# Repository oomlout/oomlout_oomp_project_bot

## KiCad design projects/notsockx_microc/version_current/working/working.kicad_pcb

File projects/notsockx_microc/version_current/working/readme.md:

# microc by notsockx  
This is a harvested standardized copy of a project from github.  
The original project can be found at:  
https://github.com/notsockx/microc  
Please consult that link for additional, details, files, and license information.  
Note: It was auto harvested and if the original repo had more than one board file or anything out of the ordinary the files here are likely not representative.

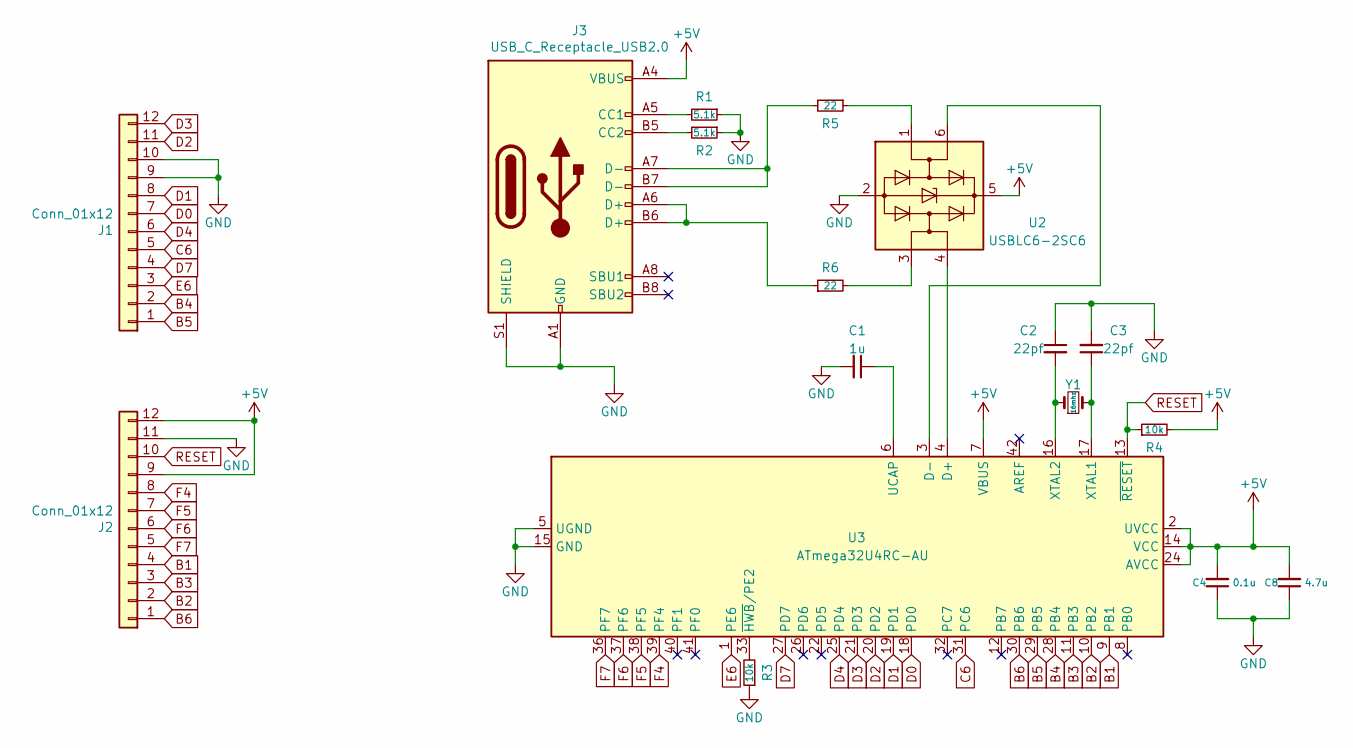
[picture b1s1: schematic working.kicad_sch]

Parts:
C1: 1u; C_0603_1608Metric
C2, C3: 22pf; C_0603_1608Metric
C4: 0.1u; C_0603_1608Metric
C8: 4.7u; C_0603_1608Metric
J1, J2: Conn_01x12; PinSocket_1x12_P2.54mm_Vertical
J3: USB_C_Receptacle_USB2.0; USB-C_16P_Midmount
R1, R2: 5.1k; R_0603_1608Metric
R3, R4: 10k; R_0603_1608Metric
R5, R6: 22; R_0603_1608Metric
U2: USBLC6-2SC6; SOT-23-6
U3: ATmega32U4RC-AU; TQFP-44_10x10mm_P0.8mm
Y1: 16mhz; Crystal_SMD_5032-2Pin_5.0x3.2mm_HandSoldering

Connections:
B1: J2.4, U3.9 (PB1)
B2: J2.2, U3.10 (PB2)
B3: J2.3, U3.11 (PB3)
B4: J1.2, U3.28 (PB4)
B5: J1.1, U3.29 (PB5)
B6: J2.1, U3.30 (PB6)
C6: J1.5, U3.31 (PC6)
D0: J1.7, U3.18 (PD0)
D1: J1.8, U3.19 (PD1)
D2: J1.11, U3.20 (PD2)
D3: J1.12, U3.21 (PD3)
D4: J1.6, U3.25 (PD4)
D7: J1.4, U3.27 (PD7)
E6: J1.3, U3.1 (PE6)
F4: J2.8, U3.39 (PF4)
F5: J2.7, U3.38 (PF5)
F6: J2.6, U3.37 (PF6)
F7: J2.5, U3.36 (PF7)
GND: C1.2, C2.1, C3.2, C4.1, C8.1, J1.9, J1.10, J2.11, J3.A1 (GND), J3.A12 (GND), J3.B1 (GND), J3.B12 (GND), J3.S1 (SHIELD), R3.1, U2.2 (GND), U3.5 (UGND), U3.15 (GND), U3.23 (GND), U3.35 (GND), U3.43 (GND)
unnamed: C1.1, U3.6 (UCAP)
unnamed: C2.2, U3.16 (XTAL2), Y1.1
unnamed: C3.1, U3.17 (XTAL1), Y1.2
unnamed: J3.A5 (CC1), R1.2
unnamed: J3.A6 (D+), J3.B6 (D+), R6.1
unnamed: J3.A7 (D-), J3.B7 (D-), R5.2
unnamed: J3.B5 (CC2), R2.2
unnamed: R3.2, U3.33 (~HWB/PE2)
unnamed: R5.1, U2.1 (I/O1)
unnamed: R6.2, U2.3 (I/O2)
unnamed: U2.4 (I/O2), U3.4 (D+)
unnamed: U2.6 (I/O1), U3.3 (D-)
RESET: J2.10, R4.1, U3.13 (~RESET)

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
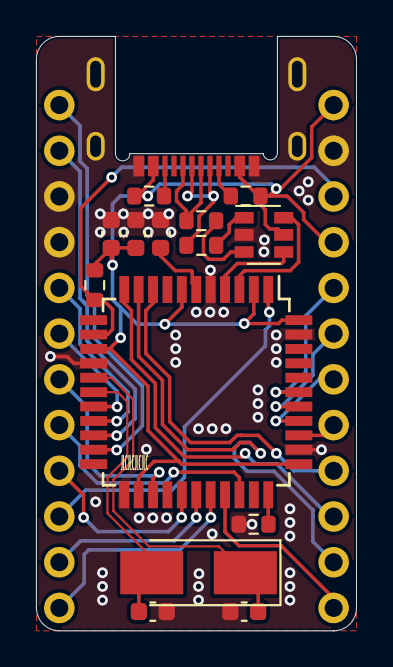
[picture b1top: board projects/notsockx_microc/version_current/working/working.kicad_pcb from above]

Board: 2 copper layers, 17.8 x 33.0 mm, 17 parts (0 on the bottom side), 33 nets.

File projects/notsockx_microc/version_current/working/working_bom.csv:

"Id";"Designator";"Footprint";"Quantity";"Designation";"Supplier and ref";
1;"J2,J1";"PinSocket_1x12_P2.54mm_Vertical";2;"Conn_01x12";;;
2;"U3";"TQFP-44_10x10mm_P0.8mm";1;"ATmega32U4RC-AU";;;
3;"Y1";"Crystal_SMD_5032-2Pin_5.0x3.2mm_HandSoldering";1;"16mhz";;;
4;"C3,C2";"C_0603_1608Metric";2;"22pf";;;
5;"R6,R5";"R_0603_1608Metric";2;"22";;;
6;"R4,R3";"R_0603_1608Metric";2;"10k";;;
7;"R2,R1";"R_0603_1608Metric";2;"5.1k";;;
8;"C8";"C_0603_1608Metric";1;"4.7u";;;
9;"C4";"C_0603_1608Metric";1;"0.1u";;;
10;"C1";"C_0603_1608Metric";1;"1u";;;
11;"J3";"USB-C_16P_Midmount";1;"USB_C_Receptacle_USB2.0";;;
12;"U2";"SOT-23-6";1;"USBLC6-2SC6";;;

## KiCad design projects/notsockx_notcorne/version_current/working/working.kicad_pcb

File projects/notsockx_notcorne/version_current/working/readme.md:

# OOMP Project  
## notcorne  by notsockx  
  
oomp key: oomp_projects_flat_notsockx_notcorne  
(snippet of original readme)  
  
- notcorne  
Corne-styled Kailh Choc switch keyboard.  
  
- Features  
MCU: ATMega32u4 (Pro Micro) <br />  
Switches: Kailh Choc <br />  
Connectivity: RJ11 for both halves <br />  
  
- To-do  
- Adjust collum stagger  
- Adjust thumb cluster  
  
  full source readme at [readme_src.md](readme_src.md)  
  
source repo at: [https://github.com/notsockx/notcorne](https://github.com/notsockx/notcorne)  
## Board  

## Schematic  

[schematic pdf](working_schematic.pdf)  
## Images

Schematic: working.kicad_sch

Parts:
B1: SPARKFUN_PRO_MICRO
D1, D2, D3, D4, D5, D6, D7, D8, D9, D10, D11, D12, D13, D14, D15, D16, D17, D18, D19, D20, D21: D_Small; D_T-1_P5.08mm_Horizontal
H1, H2, H3, H4, H5, H6, H7: MountingHole; MountingHole_2.2mm_M2
J1: AudioJack4; Jack_3.5mm_PJ320D_Horizontal
JP1, JP2: SolderJumper_3_Open; PinHeader_1x03_P1.00mm_Vertical
SW1, SW2, SW3, SW4, SW5, SW6, SW7, SW8, SW9, SW10, SW11, SW12, SW13, SW14, SW15, SW16, SW17, SW18, SW19, SW20, SW21: SW_Push; SW_PG1350_reversible

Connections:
+5V: J1.T, JP1.2 (C)
GND: B1.3, B1.23, J1.S
unnamed: B1.1, JP2.3 (B)
unnamed: B1.4, JP1.1 (A)
unnamed: B1.21, JP1.3 (B)
unnamed: B1.24, JP2.1 (A)
unnamed: D1.2 (A), SW1.1
unnamed: D2.2 (A), SW2.1
unnamed: D3.2 (A), SW3.1
unnamed: D4.2 (A), SW4.1
unnamed: D5.2 (A), SW5.1
unnamed: D6.2 (A), SW6.1
unnamed: D7.2 (A), SW7.1
unnamed: D8.2 (A), SW8.1
unnamed: D9.2 (A), SW9.1
unnamed: D10.2 (A), SW10.1
unnamed: D11.2 (A), SW11.1
unnamed: D12.2 (A), SW12.1
unnamed: D13.2 (A), SW13.1
unnamed: D14.2 (A), SW14.1
unnamed: D15.2 (A), SW15.1
unnamed: D16.2 (A), SW16.1
unnamed: D17.2 (A), SW17.1
unnamed: D18.2 (A), SW18.1
unnamed: D19.2 (A), SW19.1
unnamed: D20.2 (A), SW20.1
unnamed: D21.2 (A), SW21.1
TX: J1.R1, JP2.2 (C)
col0: B1.12, SW1.2, SW2.2, SW3.2
col1: B1.11, SW4.2, SW5.2, SW6.2
col2: B1.10, SW7.2, SW8.2, SW9.2
col3: B1.9, SW10.2, SW11.2, SW12.2, SW13.2
col4: B1.8, SW14.2, SW15.2, SW16.2, SW17.2
col5: B1.7, SW18.2, SW19.2, SW20.2, SW21.2
row0: B1.16, D1.1 (K), D4.1 (K), D7.1 (K), D10.1 (K), D14.1 (K), D18.1 (K)
row1: B1.15, D2.1 (K), D5.1 (K), D8.1 (K), D11.1 (K), D15.1 (K), D19.1 (K)
row2: B1.14, D3.1 (K), D6.1 (K), D9.1 (K), D12.1 (K), D16.1 (K), D20.1 (K)
row3: B1.13, D13.1 (K), D17.1 (K), D21.1 (K)

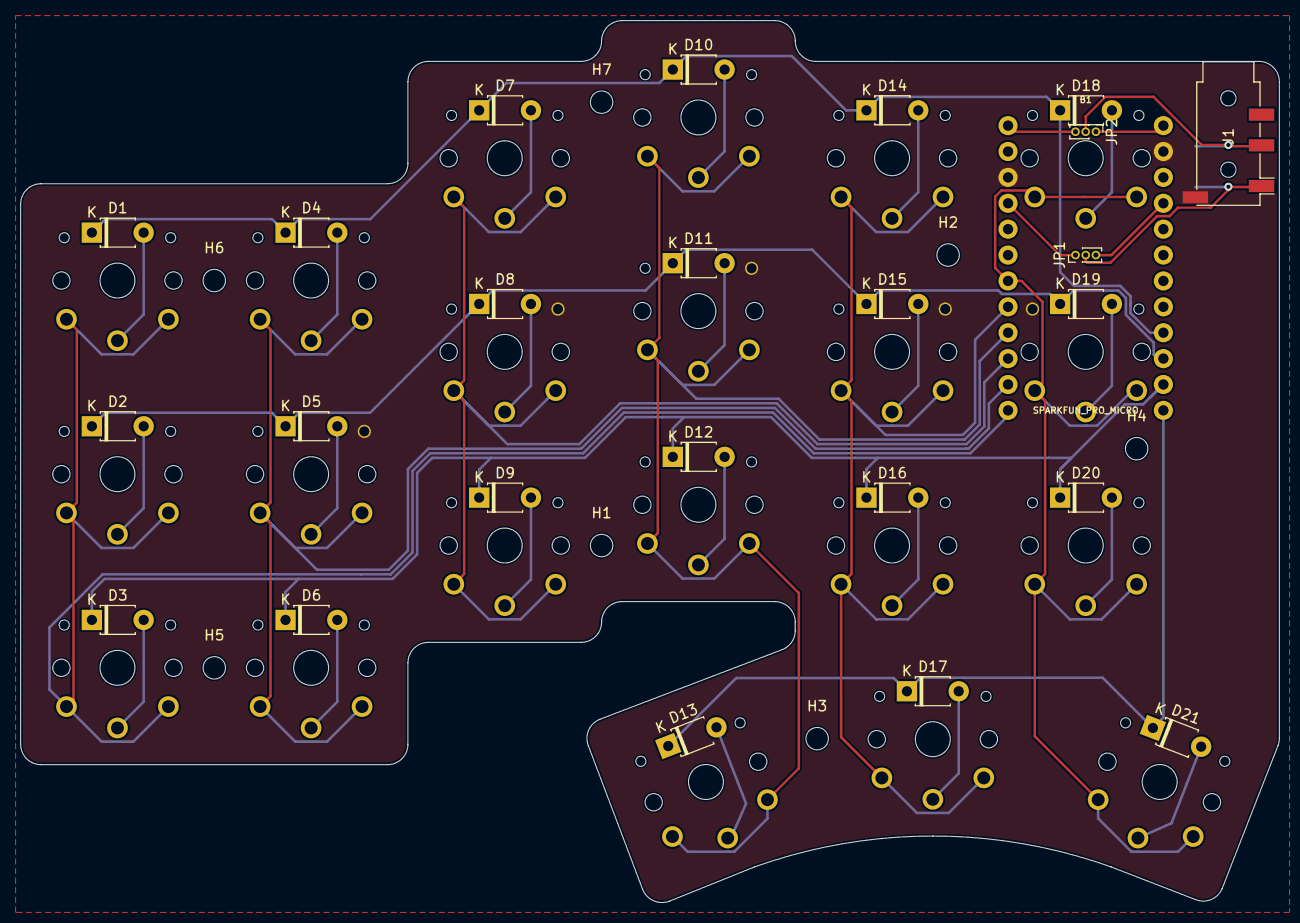
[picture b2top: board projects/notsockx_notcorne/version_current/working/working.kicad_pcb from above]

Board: 2 copper layers, 123.5 x 86.5 mm, 53 parts (0 on the bottom side), 38 nets.

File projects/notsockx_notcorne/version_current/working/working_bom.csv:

"Id";"Designator";"Footprint";"Quantity";"Designation";"Supplier and ref";
1;"SW6,SW21,SW20,SW19,SW18,SW17,SW16,SW15,SW14,SW13,SW12,SW11,SW10,SW9,SW8,SW7,SW5,SW4,SW3,SW2,SW1";"SW_PG1350_reversible";21;"SW_Push";;;
2;"JP1,JP2";"PinHeader_1x03_P1.00mm_Vertical";2;"SolderJumper_3_Open";;;
3;"J1";"Jack_3.5mm_PJ320D_Horizontal";1;"AudioJack4";;;
4;"D21,D20,D19,D18,D17,D16,D15,D14,D13,D12,D11,D10,D9,D8,D7,D6,D5,D4,D3,D2,D1";"D_T-1_P5.08mm_Horizontal";21;"D_Small";;;

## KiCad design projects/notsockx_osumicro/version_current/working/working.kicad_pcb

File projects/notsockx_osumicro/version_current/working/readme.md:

# osumicro by notsockx  
This is a harvested standardized copy of a project from github.  
The original project can be found at:  
https://github.com/notsockx/osumicro  
Please consult that link for additional, details, files, and license information.  
Note: It was auto harvested and if the original repo had more than one board file or anything out of the ordinary the files here are likely not representative.

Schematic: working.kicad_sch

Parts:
H1, H2, H3, H4: MountingHole; MountingHole_2.2mm_M2_DIN965
SW1, SW2: SW_Push; Kailh_socket_MX_optional
U1: Sparkfun_Pro_Micro

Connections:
GND: U1.3, U1.4, U1.23
unnamed: SW1.1, U1.20
unnamed: SW1.2, SW2.2, U1.19
unnamed: SW2.1, U1.18

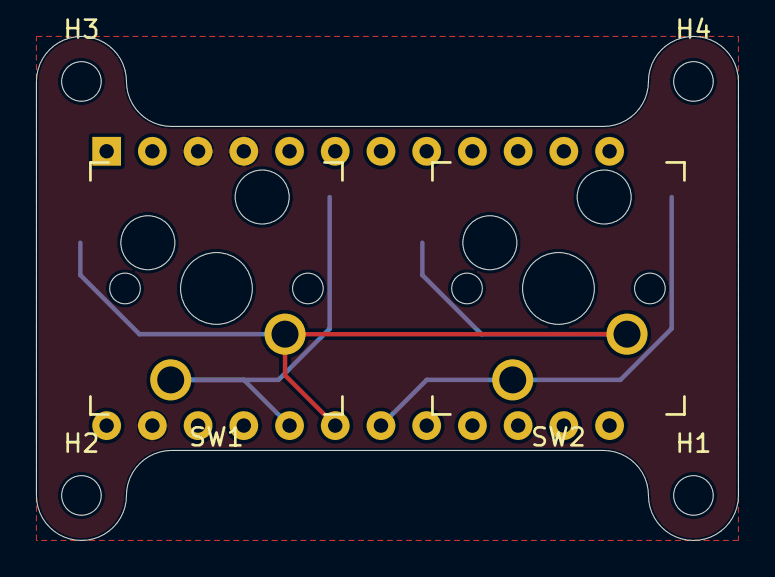
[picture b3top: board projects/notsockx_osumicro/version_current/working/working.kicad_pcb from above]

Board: 2 copper layers, 39.0 x 28.0 mm, 7 parts (1 on the bottom side), 4 nets.

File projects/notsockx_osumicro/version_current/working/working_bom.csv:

"Id";"Designator";"Footprint";"Quantity";"Designation";"Supplier and ref";
1;"SW2,SW1";"Kailh_socket_MX_optional";2;"SW_Push";;;
2;"U1";"Sparkfun_Pro_Micro";1;"Sparkfun_Pro_Micro";;;

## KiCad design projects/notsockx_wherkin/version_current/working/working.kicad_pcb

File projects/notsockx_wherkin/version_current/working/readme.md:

# wherkin by notsockx  
This is a harvested standardized copy of a project from github.  
The original project can be found at:  
https://github.com/notsockx/wherkin  
Please consult that link for additional, details, files, and license information.  
Note: It was auto harvested and if the original repo had more than one board file or anything out of the ordinary the files here are likely not representative.

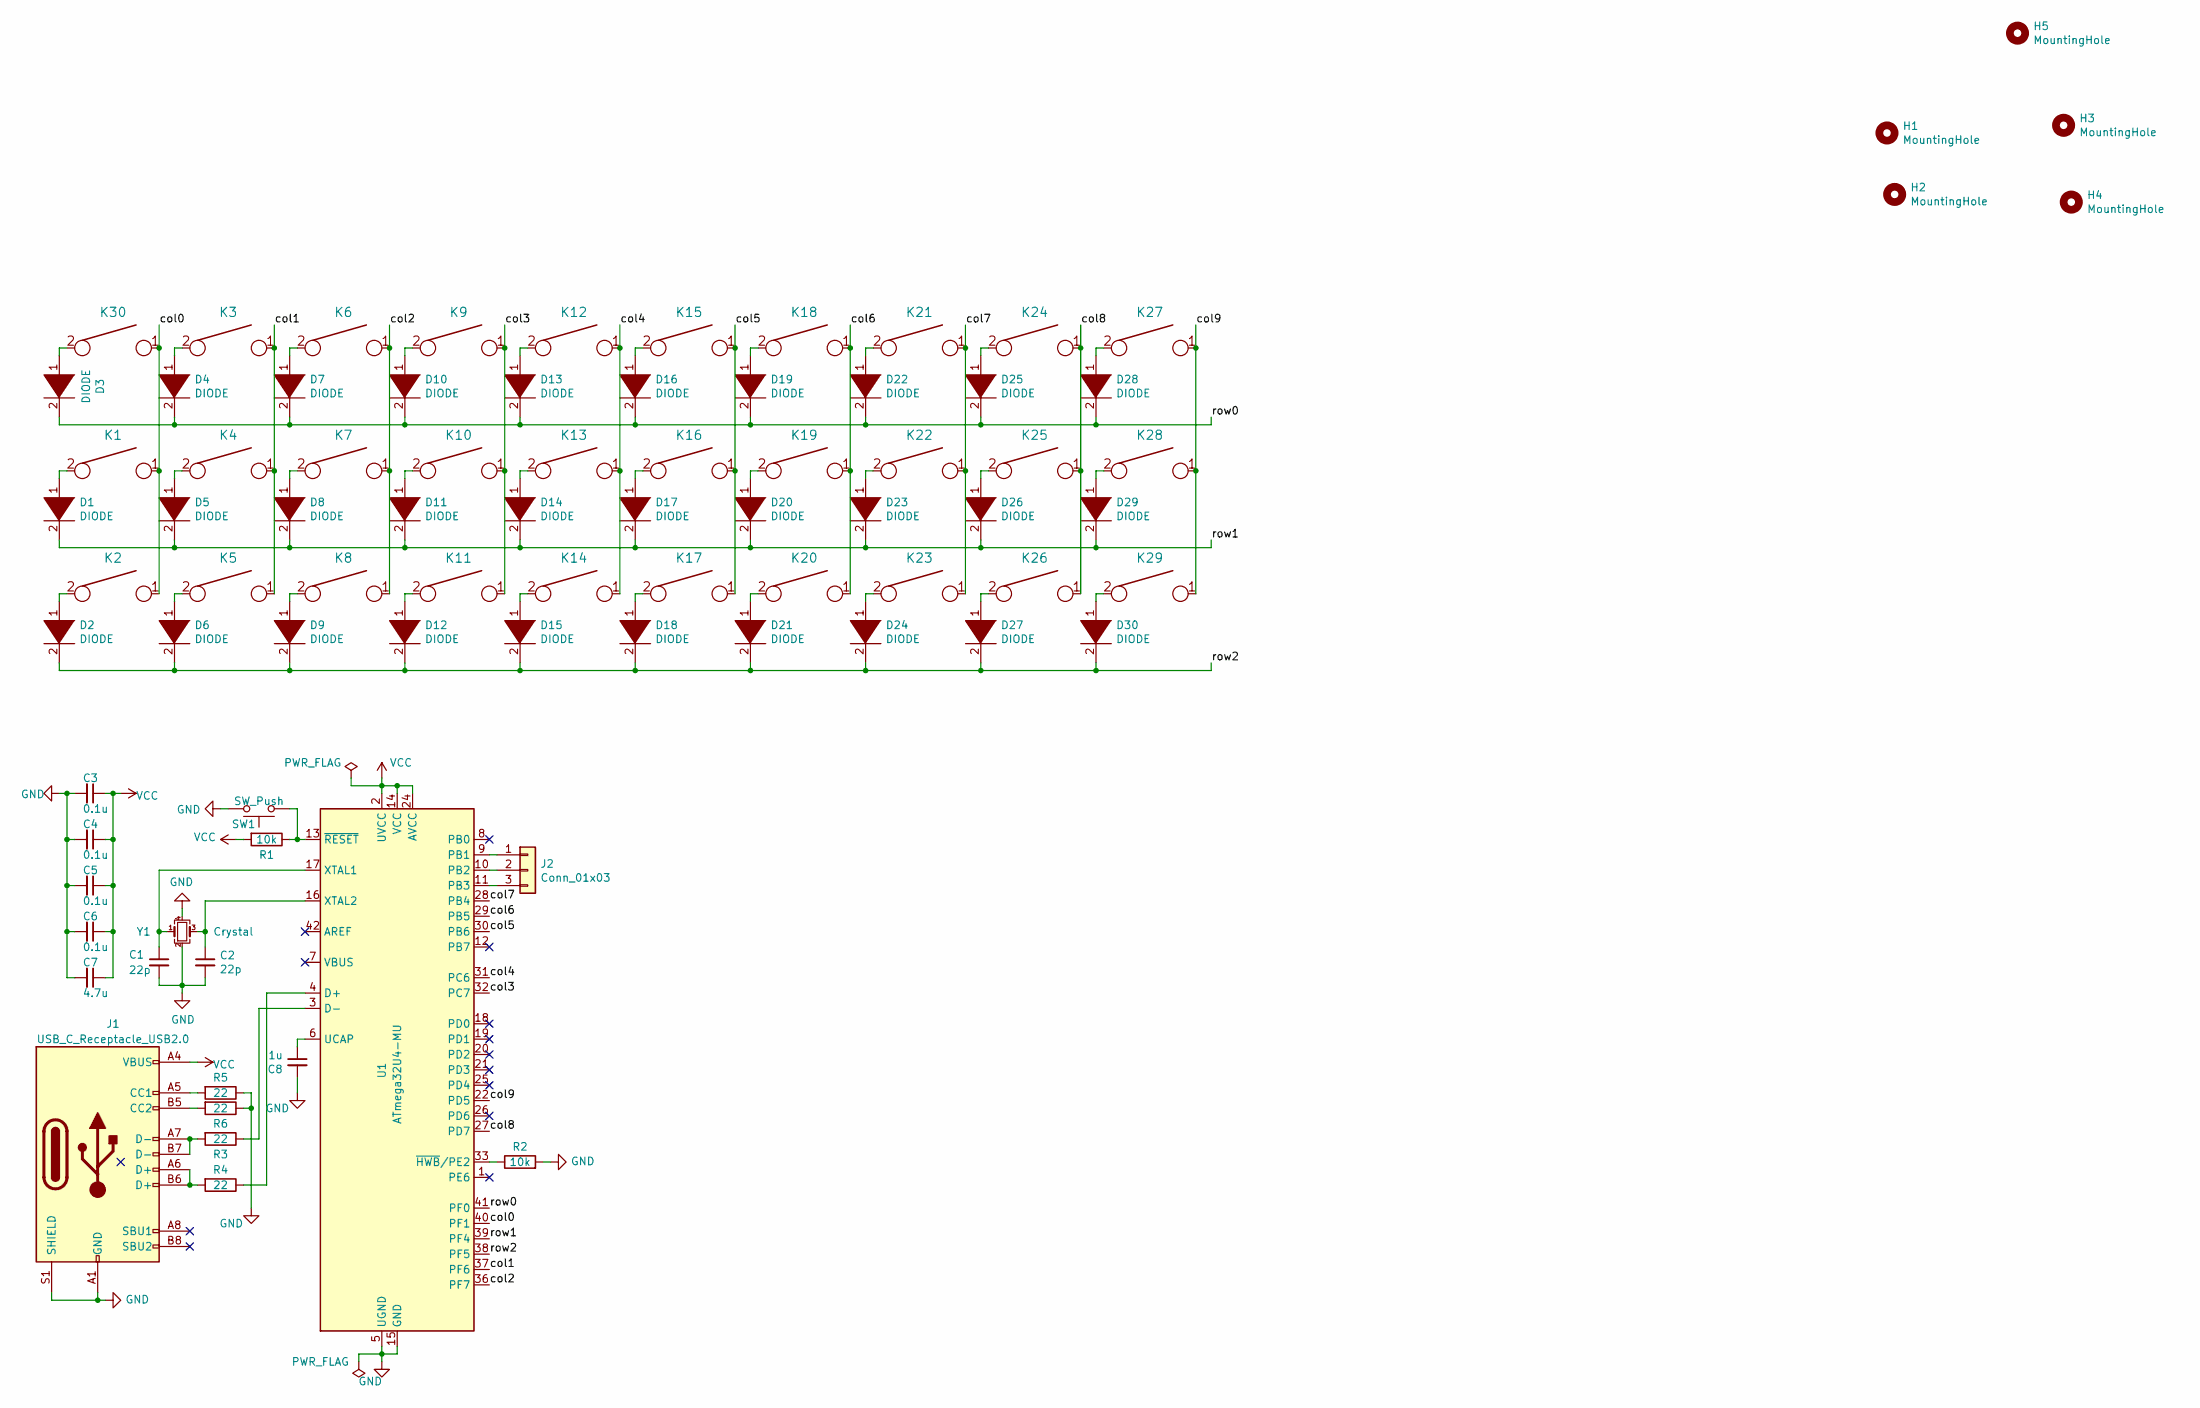
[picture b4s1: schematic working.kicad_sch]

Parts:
C1, C2: 22p; C_0603_1608Metric_Pad1.05x0.95mm_HandSolder
C3, C4, C5, C6: 0.1u; C_0603_1608Metric_Pad1.05x0.95mm_HandSolder
C7: 4.7u; C_0603_1608Metric_Pad1.05x0.95mm_HandSolder
C8: 1u; C_0603_1608Metric_Pad1.05x0.95mm_HandSolder
D1, D2, D3, D4, D5, D6, D7, D8, D9, D10, D11, D12, D13, D14, D15, D16, D17, D18, D19, D20, D21, D22, D23, D24, D25, D26, D27, D28, D29, D30: DIODE; D_0201_0603Metric
H1, H2, H3, H4, H5: MountingHole; MountingHole_2.2mm_M2
J1: USB_C_Receptacle_USB2.0; USB_C_Receptacle_HRO_TYPE-C-31-M-12_hand_solder
J2: Conn_01x03; PinHeader_1x03_P1.00mm_Vertical
K1, K2, K3, K4, K5, K6, K7, K8, K9, K10, K11, K12, K13, K14, K15, K16, K17, K18, K19, K20, K21, K22, K23, K24, K25, K26, K27, K28, K29, K30: KEYSW; Kailh_socket_MX
R1, R2: 10k; R_0603_1608Metric_Pad1.05x0.95mm_HandSolder
R3, R4, R5, R6: 22; R_0603_1608Metric_Pad1.05x0.95mm_HandSolder
SW1: SW_Push; SW_Push_1P1T_NO_CK_KMR2
U1: ATmega32U4-MU; QFN-44-1EP_7x7mm_P0.5mm_EP5.2x5.2mm
Y1: Crystal; Crystal_SMD_3225-4Pin_3.2x2.5mm_HandSoldering

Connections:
/col0: K1.1, K2.1, K30.1, U1.40 (PF1)
/col1: K3.1, K4.1, K5.1, U1.37 (PF6)
/col2: K6.1, K7.1, K8.1, U1.36 (PF7)
/col3: K9.1, K10.1, K11.1, U1.32 (PC7)
/col4: K12.1, K13.1, K14.1, U1.31 (PC6)
/col5: K15.1, K16.1, K17.1, U1.30 (PB6)
/col6: K18.1, K19.1, K20.1, U1.29 (PB5)
/col7: K21.1, K22.1, K23.1, U1.28 (PB4)
/col8: K24.1, K25.1, K26.1, U1.27 (PD7)
/col9: K27.1, K28.1, K29.1, U1.22 (PD5)
/row0: D3.2 (A), D4.2 (A), D7.2 (A), D10.2 (A), D13.2 (A), D16.2 (A), D19.2 (A), D22.2 (A), D25.2 (A), D28.2 (A), U1.41 (PF0)
/row1: D1.2 (A), D5.2 (A), D8.2 (A), D11.2 (A), D14.2 (A), D17.2 (A), D20.2 (A), D23.2 (A), D26.2 (A), D29.2 (A), U1.39 (PF4)
/row2: D2.2 (A), D6.2 (A), D9.2 (A), D12.2 (A), D15.2 (A), D18.2 (A), D21.2 (A), D24.2 (A), D27.2 (A), D30.2 (A), U1.38 (PF5)
GND: C1.2, C2.2, C3.2, C4.2, C5.2, C6.2, C7.2, C8.2, J1.A1 (GND), J1.A12 (GND), J1.B1 (GND), J1.B12 (GND), J1.S1 (SHIELD), R2.2, R5.1, R6.1, SW1.2, U1.5 (UGND), U1.15 (GND), U1.23 (GND), U1.35 (GND), U1.43 (GND), U1.45 (GND), Y1.2, Y1.4
unnamed: C1.1, U1.17 (XTAL1), Y1.1
unnamed: C2.1, U1.16 (XTAL2), Y1.3
unnamed: C8.1, U1.6 (UCAP)
unnamed: D1.1 (K), K1.2
unnamed: D2.1 (K), K2.2
unnamed: D3.1 (K), K30.2
unnamed: D4.1 (K), K3.2
unnamed: D5.1 (K), K4.2
unnamed: D6.1 (K), K5.2
unnamed: D7.1 (K), K6.2
unnamed: D8.1 (K), K7.2
unnamed: D9.1 (K), K8.2
unnamed: D10.1 (K), K9.2
unnamed: D11.1 (K), K10.2
unnamed: D12.1 (K), K11.2
unnamed: D13.1 (K), K12.2
unnamed: D14.1 (K), K13.2
unnamed: D15.1 (K), K14.2
unnamed: D16.1 (K), K15.2
unnamed: D17.1 (K), K16.2
unnamed: D18.1 (K), K17.2
unnamed: D19.1 (K), K18.2
unnamed: D20.1 (K), K19.2
unnamed: D21.1 (K), K20.2
unnamed: D22.1 (K), K21.2
unnamed: D23.1 (K), K22.2
unnamed: D24.1 (K), K23.2
unnamed: D25.1 (K), K24.2
unnamed: D26.1 (K), K25.2
unnamed: D27.1 (K), K26.2
unnamed: D28.1 (K), K27.2
unnamed: D29.1 (K), K28.2
unnamed: D30.1 (K), K29.2
unnamed: J1.A5 (CC1), R5.2
unnamed: J1.A6 (D+), J1.B6 (D+), R4.2
unnamed: J1.A7 (D-), J1.B7 (D-), R3.2
unnamed: J1.B5 (CC2), R6.2
unnamed: J2.1, U1.9 (PB1)
unnamed: J2.2, U1.10 (PB2)
unnamed: J2.3, U1.11 (PB3)
unnamed: R1.1, SW1.1, U1.13 (~RESET)
unnamed: R2.1, U1.33 (~HWB/PE2)
unnamed: R3.1, U1.3 (D-)
unnamed: R4.1, U1.4 (D+)
VCC: C3.1, C4.1, C5.1, C6.1, C7.1, J1.A4 (VBUS), J1.A9 (VBUS), J1.B4 (VBUS), J1.B9 (VBUS), R1.2, U1.2 (UVCC), U1.14 (VCC), U1.24 (AVCC), U1.34 (VCC), U1.44 (AVCC)

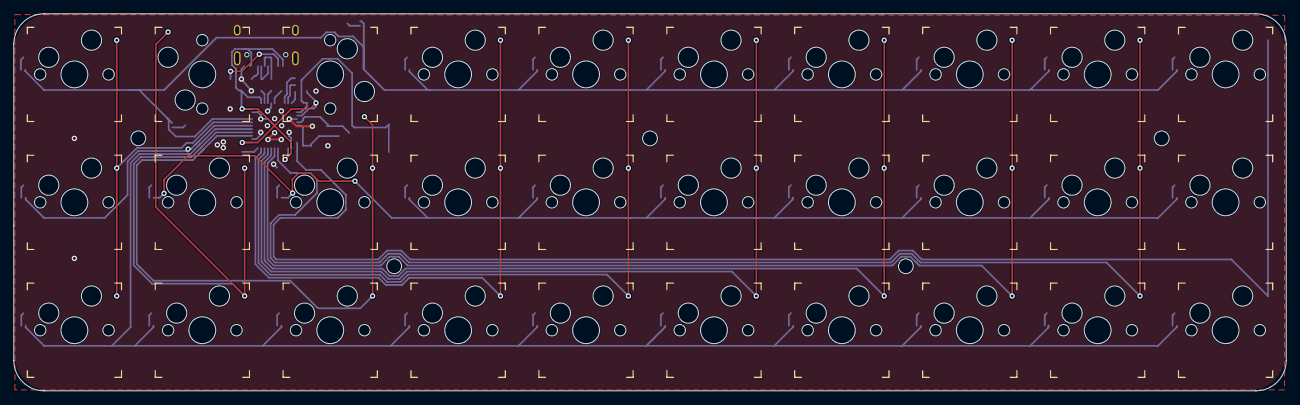
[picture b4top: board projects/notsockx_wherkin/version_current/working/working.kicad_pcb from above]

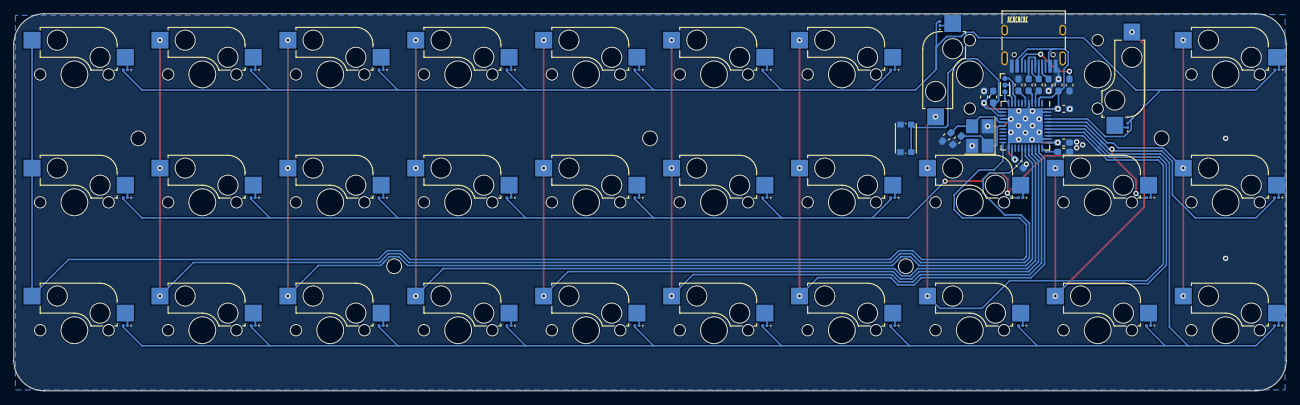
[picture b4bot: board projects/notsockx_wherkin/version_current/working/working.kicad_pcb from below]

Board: 2 copper layers, 189.0 x 56.0 mm, 84 parts (53 on the bottom side), 59 nets.

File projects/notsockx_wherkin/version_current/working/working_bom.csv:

"Id";"Designator";"Footprint";"Quantity";"Designation";"Supplier and ref";
1;"R6,R5,R4,R3";"R_0603_1608Metric_Pad1.05x0.95mm_HandSolder";4;"22";;;
2;"K3,K4,K5,K6,K30,K29,K28,K27,K26,K25,K24,K23,K22,K21,K20,K19,K18,K17,K16,K15,K14,K13,K12,K11,K10,K9,K8,K7,K2,K1";"Kailh_socket_MX";30;"KEYSW";;;
3;"J2";"PinHeader_1x03_P1.00mm_Vertical";1;"Conn_01x03";;;
4;"Y1";"Crystal_SMD_3225-4Pin_3.2x2.5mm_HandSoldering";1;"Crystal";;;
5;"U1";"QFN-44-1EP_7x7mm_P0.5mm_EP5.2x5.2mm";1;"ATmega32U4-MU";;;
6;"SW1";"SW_Push_1P1T_NO_CK_KMR2";1;"SW_Push";;;
7;"R2,R1";"R_0603_1608Metric_Pad1.05x0.95mm_HandSolder";2;"10k";;;
8;"J1";"USB_C_Receptacle_HRO_TYPE-C-31-M-12_hand_solder";1;"USB_C_Receptacle_USB2.0";;;
9;"D30,D29,D28,D27,D26,D25,D24,D23,D22,D21,D20,D19,D18,D17,D16,D15,D14,D13,D12,D11,D10,D9,D8,D7,D6,D5,D4,D3,D2,D1";"D_0201_0603Metric";30;"DIODE";;;
10;"C8";"C_0603_1608Metric_Pad1.05x0.95mm_HandSolder";1;"1u";;;
11;"C7";"C_0603_1608Metric_Pad1.05x0.95mm_HandSolder";1;"4.7u";;;
12;"C6,C5,C4,C3";"C_0603_1608Metric_Pad1.05x0.95mm_HandSolder";4;"0.1u";;;
13;"C2,C1";"C_0603_1608Metric_Pad1.05x0.95mm_HandSolder";2;"22p";;;

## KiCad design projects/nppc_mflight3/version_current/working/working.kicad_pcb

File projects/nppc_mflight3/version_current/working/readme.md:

# Mflight3 by nppc  
This is a harvested standardized copy of a project from github.  
The original project can be found at:  
https://github.com/nppc/Mflight3  
Please consult that link for additional, details, files, and license information.  
Note: It was auto harvested and if the original repo had more than one board file or anything out of the ordinary the files here are likely not representative.

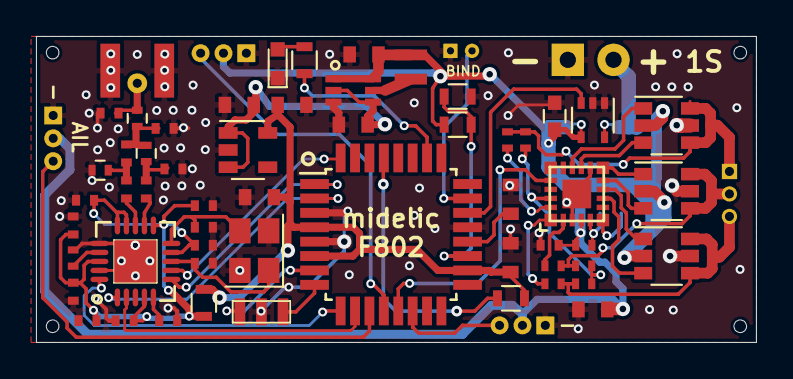
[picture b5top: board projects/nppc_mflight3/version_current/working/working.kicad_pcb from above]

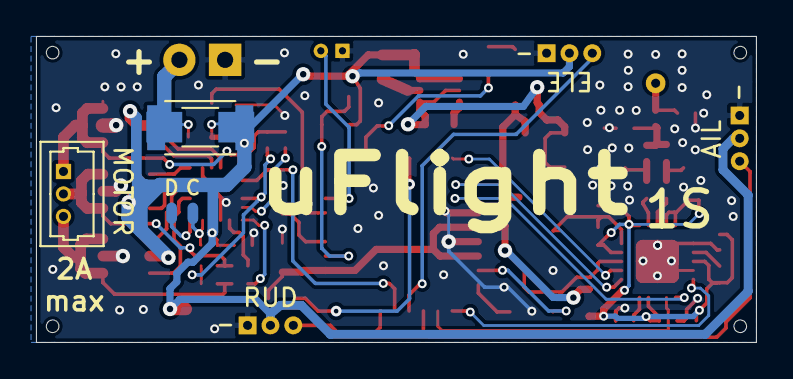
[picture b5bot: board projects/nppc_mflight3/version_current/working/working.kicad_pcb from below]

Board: 2 copper layers, 40.0 x 17.0 mm, 66 parts (8 on the bottom side), 50 nets.

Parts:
AE1: ANT; ANT_PCB
C1, C3, C25: 10uf; C_0603
C2: 10n; C_0603
C4: 100n; C_0603
C5, C6, C7: 2uf; C_0603
C8, C10, C16, C17, C26: 100n; C_0402
C9: 2uf; C_0402
C11, C14: 27p; C_0402
C12, C13, C15: 220p; C_0402
C18, C19: 100p; C_0402
C20, C21: 1p; C_0402
C22, C23: 1.8p; C_0402
C24: 47uf; C_0603
D1: LED; LED_0603
J1: C2CK; PAD_1.2X0.6_Round
J2: C2D; PAD_1.2X0.6_Round
J3: MOTOR; Molex_PicoBlade_53047-0310_03x1.25mm_Straight
J6: BIND; Conn2pin_small
J7: BAT; Conn_1x02_2.54mm
J8: SRV1; Pin_Header_Straight_1x03_Pitch1.27mm
J9: SRV2; Pin_Header_Straight_1x03_Pitch1.27mm
J10: SRV3; Pin_Header_Straight_1x03_Pitch1.27mm
L1: 4.7uH; InductorXFL2006
L2: 1000; L_0603
L3, L4, L5: 1.2n; L_0402
Q1, Q2, Q3: DUAL_NP; SuperSOT-6
R1, R4: 10K; R_0603
R2: 18K; R_0603
R3: 1K; R_0603
R5: 56K; R_0402_NoSilk
R6, R7, R9, R11: 1K; R_0402_NoSilk
R8, R10, R12: 10K; R_0402_NoSilk
R13: 0.022; R_1206_HandSoldering
R14: 0.022; R_2010
U1: TPS61222; SC-70-6
U2: ATmega328P-AU; TQFP-32_7x7mm_Pitch0.8mm
U3: RT9013-33; SOT-23-5
U4: CC2500
U5: EFM8BB21; QFN20
U6: MAX9610; SOT-353_SC-70-5
Y1: 16MHZ; Ceramic_Resonator_SMD_3mm
Y2: 26MHZ; Crystal_SMD_SeikoEpson_FA238-4pin_3.2x2.5mm

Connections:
+3V3: C4.1, C6.1, C7.1, L2.1, R4.1, U2.4, U2.6, U2.18, U3.5
+BATT: C1.1, C24.2, C25.2, C26.2, J8.2, J9.2, J10.2, L1.1, Q1.2, Q2.2, Q3.2, R1.2, R6.1, R13.1, R14.1, U1.1, U1.6, U5.4, U6.4
/5V: C3.1, C5.1, U1.2, U1.4, U3.1, U3.3
/A1: R1.1, R2.2, U2.19
/A2: U2.22, U6.3
/CH1: J8.3, U2.11
/CH2: J9.3, U2.12
/CH3: U2.13, U5.17
/CH4: J10.3, U2.14
/CSN: U2.32, U4.7
/GDO0: U2.1, U4.6
/SCLK: U2.2, U4.1
/SI: U2.9, U4.20
/SO: U2.10, U4.2
/uESC1S/Ac: Q1.3, U5.13
/uESC1S/Ap: Q1.1, U5.14
/uESC1S/Bc: Q2.3, U5.10
/uESC1S/Bp: Q2.1, U5.11
/uESC1S/Cc: Q3.3, U5.8
/uESC1S/Cp: Q3.1, U5.9
/uESC1S/M_A: J3.1, Q1.4, Q1.6, R7.2, R8.1
/uESC1S/M_B: J3.2, Q2.4, Q2.6, R9.2, R10.1
/uESC1S/M_C: J3.3, Q3.4, Q3.6, R11.2, R12.1
GND: AE1.2, C1.2, C2.2, C3.2, C4.2, C5.2, C6.2, C7.2, C8.1, C9.2, C10.1, C11.1, C12.2, C13.1, C14.1, C15.2, C16.1, C17.1, C20.1, C22.1, C23.1, C24.1, C25.1, C26.1, D1.1, J6.1, J7.1, J8.1, J9.1, J10.1, L3.2, Q1.5, Q2.5, Q3.5, R2.1, R5.1, U1.3, U2.3, U2.5, U2.21, U3.2, U4.16, U4.19, U5.3, U5.12, U5.21, U6.1, U6.2, Y1.2, Y2.2, Y2.4
unnamed: AE1.1, C23.2, L5.2
unnamed: C2.1, U2.20
unnamed: C10.2, U4.5
unnamed: C11.2, U4.8, Y2.1
unnamed: C14.2, U4.10, Y2.3
unnamed: C18.1, C21.2, L3.1
unnamed: C18.2, U4.13
unnamed: C19.1, C20.2, L4.1
unnamed: C19.2, U4.12
unnamed: C21.1, C22.2, L4.2, L5.1
unnamed: D1.2, R3.1
unnamed: J1.1, R6.2, U5.5
unnamed: J2.1, U5.6
unnamed: J6.2, U2.23
unnamed: J7.2, R13.2, R14.2, U6.5
unnamed: L1.2, U1.5
unnamed: R3.2, U2.26
unnamed: R4.2, U2.29
unnamed: R5.2, U4.17
unnamed: R8.2, U5.20
unnamed: R10.2, U5.2
unnamed: R7.1, R9.1, R11.1, U5.19
unnamed: R12.2, U5.1
unnamed: U2.7, Y1.3
unnamed: U2.8, Y1.1
VCC: C8.2, C9.1, C12.1, C13.2, C15.1, C16.2, C17.2, L2.2, U4.4, U4.9, U4.11, U4.14, U4.15, U4.18

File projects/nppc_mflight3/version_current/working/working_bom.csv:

"Id";"Designator";"Footprint";"Quantity";"Designation";"Supplier and ref";
1;"C20,C21";"C_0402";2;"1p";;;
2;"J7";"Conn_1x02_2.54mm";1;"BAT";;;
3;"J10";"Pin_Header_Straight_1x03_Pitch1.27mm";1;"SRV3";;;
4;"J8";"Pin_Header_Straight_1x03_Pitch1.27mm";1;"SRV1";;;
5;"J9";"Pin_Header_Straight_1x03_Pitch1.27mm";1;"SRV2";;;
6;"AE1";"ANT_PCB";1;"ANT";;;
7;"J3";"Molex_PicoBlade_53047-0310_03x1.25mm_Straight";1;"MOTOR";;;
8;"C25,C1,C3";"C_0603";3;"10uf";;;
9;"C26,C8,C10,C16,C17";"C_0402";5;"100n";;;
10;"C2";"C_0603";1;"10n";;;
11;"C4";"C_0603";1;"100n";;;
12;"C5,C6,C7";"C_0603";3;"2uf";;;
13;"C11,C14";"C_0402";2;"27p";;;
14;"C12,C13,C15";"C_0402";3;"220p";;;
15;"C18,C19";"C_0402";2;"100p";;;
16;"C22,C23";"C_0402";2;"1.8p";;;
17;"C9";"C_0402";1;"2uf";;;
18;"J2";"PAD_1.2X0.6_Round";1;"C2D";;;
19;"Y2";"Crystal_SMD_SeikoEpson_FA238-4pin_3.2x2.5mm";1;"26MHZ";;;
20;"R13";"R_1206_HandSoldering";1;"0.022";;;
21;"U5";"QFN20";1;"EFM8BB21";;;
22;"U6";"SOT-353_SC-70-5";1;"MAX9610";;;
23;"R14";"R_2010";1;"0.022";;;
24;"Y1";"Ceramic_Resonator_SMD_3mm";1;"16MHZ";;;
25;"U4";"CC2500";1;"CC2500";;;
26;"U3";"SOT-23-5";1;"RT9013-33";;;
27;"U2";"TQFP-32_7x7mm_Pitch0.8mm";1;"ATmega328P-AU";;;
28;"U1";"SC-70-6";1;"TPS61222";;;
29;"R12,R10,R8";"R_0402_NoSilk";3;"10K";;;
30;"R11,R9,R7,R6";"R_0402_NoSilk";4;"1K";;;
31;"R5";"R_0402_NoSilk";1;"56K";;;
32;"R4,R1";"R_0603";2;"10K";;;
33;"R3";"R_0603";1;"1K";;;
34;"R2";"R_0603";1;"18K";;;
35;"Q3,Q2,Q1";"SuperSOT-6";3;"DUAL_NP";;;
36;"L5,L4,L3";"L_0402";3;"1.2n";;;
37;"L2";"L_0603";1;"1000";;;
38;"L1";"InductorXFL2006";1;"4.7uH";;;
39;"J6";"Conn2pin_small";1;"BIND";;;
40;"J1";"PAD_1.2X0.6_Round";1;"C2CK";;;
41;"D1";"LED_0603";1;"LED";;;
42;"C24";"C_0603";1;"47uf";;;

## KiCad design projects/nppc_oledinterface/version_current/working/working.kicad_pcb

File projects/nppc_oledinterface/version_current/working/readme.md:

# OLEDInterface by nppc  
This is a harvested standardized copy of a project from github.  
The original project can be found at:  
https://github.com/nppc/OLEDInterface  
Please consult that link for additional, details, files, and license information.  
Note: It was auto harvested and if the original repo had more than one board file or anything out of the ordinary the files here are likely not representative.

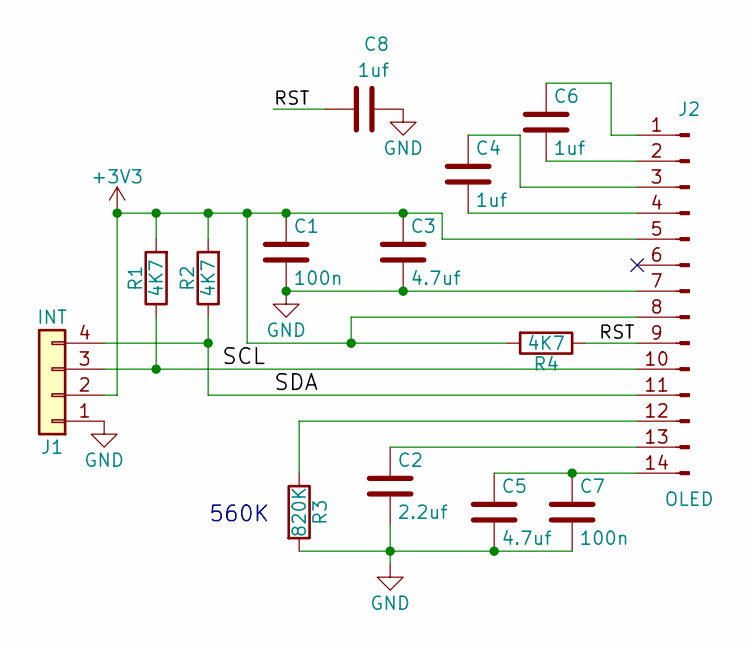
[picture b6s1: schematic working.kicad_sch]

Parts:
C1, C7: 100n; C_0402_NoSilk
C2: 2.2uf; C_0402_NoSilk
C3, C5: 4.7uf; C_0402_NoSilk
C4, C6, C8: 1uf; C_0402_NoSilk
J1: INT; SolderWirePad_4xInline_1-5mmDrill
J2: OLED; OLED_14pin
R1, R2, R4: 4K7; R_0402_NoSilk
R3: 820K; R_0402_NoSilk

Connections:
+3V3: C1.1, C3.1, J1.2, J2.5, J2.8, R1.2, R2.2, R4.2
/RST: C8.1, J2.9, R4.1
/SCL: J1.3, J2.10, R1.1
/SDA: J1.4, J2.11, R2.1
GND: C1.2, C2.2, C3.2, C5.2, C7.2, C8.2, J1.1, J2.7, R3.2
unnamed: C2.1, J2.13
unnamed: C4.1, J2.3
unnamed: C4.2, J2.4
unnamed: C5.1, C7.1, J2.14
unnamed: C6.1, J2.1
unnamed: C6.2, J2.2
unnamed: J2.12, R3.1

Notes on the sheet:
560K

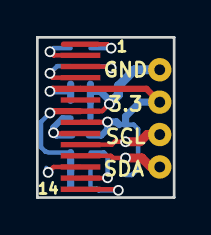
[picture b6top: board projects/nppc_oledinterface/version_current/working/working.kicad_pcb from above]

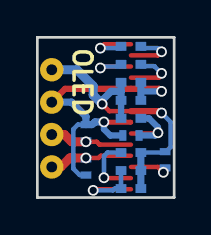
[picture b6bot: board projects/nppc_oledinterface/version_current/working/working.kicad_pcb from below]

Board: 2 copper layers, 7.6 x 8.9 mm, 14 parts (12 on the bottom side), 12 nets.

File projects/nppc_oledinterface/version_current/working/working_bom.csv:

"Id";"Designator";"Footprint";"Quantity";"Designation";"Supplier and ref";
1;"C8,C4,C6";"C_0402_NoSilk";3;"1uf";;;
2;"J2";"OLED_14pin";1;"OLED";;;
3;"J1";"conn_4pin_TH_1.8mm";1;"INT";;;
4;"C1,C7";"C_0402_NoSilk";2;"100n";;;
5;"C2";"C_0402_NoSilk";1;"2.2uf";;;
6;"C3,C5";"C_0402_NoSilk";2;"4.7uf";;;
7;"R1,R2,R4";"R_0402_NoSilk";3;"4K7";;;
8;"R3";"R_0402_NoSilk";1;"820K";;;

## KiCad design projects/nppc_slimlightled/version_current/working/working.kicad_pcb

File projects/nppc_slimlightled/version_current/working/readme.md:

# OOMP Project  
## SlimLightLED  by nppc  
  
oomp key: oomp_projects_flat_nppc_slimlightled  
(snippet of original readme)  
  
- SlimLightLED  
  
WHITE, GREEN: 20 Ohm - 45mA, 15 Ohm - 55mA.  
  
  full source readme at [readme_src.md](readme_src.md)  
  
source repo at: [https://github.com/nppc/SlimLightLED](https://github.com/nppc/SlimLightLED)  
## Board  

## Schematic  

[schematic pdf](working_schematic.pdf)  
## Images

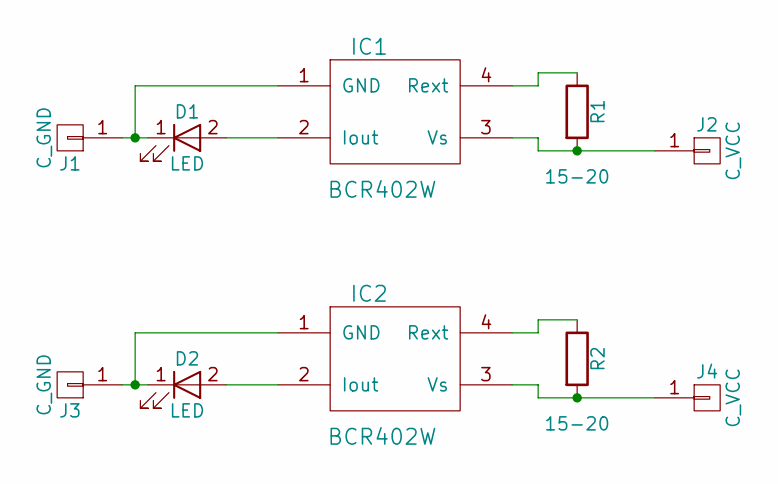
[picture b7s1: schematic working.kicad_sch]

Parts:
D1, D2: LED; 5730
IC1, IC2: BCR402W; BCR402
J1, J3: C_GND; Light_PAD
J2, J4: C_VCC; Light_PAD
R1, R2: 15-20; R_0402_NoSilk

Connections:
unnamed: D1.1 (K), IC1.1 (GND), J1.1
unnamed: D1.2 (A), IC1.2 (Iout)
unnamed: D2.1 (K), IC2.1 (GND), J3.1
unnamed: D2.2 (A), IC2.2 (Iout)
unnamed: IC1.3 (Vs), J2.1, R1.2
unnamed: IC1.4 (Rext), R1.1
unnamed: IC2.3 (Vs), J4.1, R2.2
unnamed: IC2.4 (Rext), R2.1

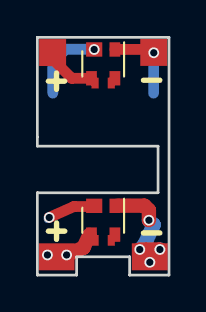
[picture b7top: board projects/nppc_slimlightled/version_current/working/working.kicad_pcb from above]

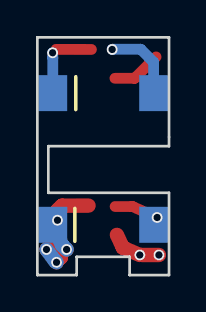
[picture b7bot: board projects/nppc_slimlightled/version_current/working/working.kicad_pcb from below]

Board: 2 copper layers, 7.3 x 13.2 mm, 10 parts (2 on the bottom side), 8 nets.

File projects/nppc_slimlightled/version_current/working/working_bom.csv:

"Id";"Designator";"Footprint";"Quantity";"Designation";"Supplier and ref";
1;"R1,R2";"R_0402_NoSilk";2;"15-20";;;
2;"D1,D2";"5730";2;"LED";;;
3;"IC1,IC2";"BCR402";2;"BCR402W";;;
4;"J2";"VCC_PAD";1;"C_VCC";;;
5;"J1";"VCC_PAD";1;"C_GND";;;
6;"J3";"Light_PAD";1;"C_GND";;;
7;"J4";"Light_PAD";1;"C_VCC";;;
